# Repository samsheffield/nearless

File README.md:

# Nearless (Nearness 1U Rework)

This is a small Intellijel 1U rework of Nearness designed by [*Jesper Särnesjö*](https://github.com/sarnesjo/nearness).

Minimal panning mixer for the Eurorack modular synthesizer system. Five inputs, two outputs. The closer an input is to either side, the greater its panning in that direction. 10hp.

Nearness is a product of the [*llllllll*](https://llllllll.co/t/prototyping-nearness-a-minimal-panning-mixer-module/8330) community.

## CHANGES

The module has been redesigned to fit an Intellijel 1U in 10hp, so there are two fewer inputs. Why 10hp? That's all I had free! :)

The resistor values have been simplified to accomodate the simple stereo spread. I tried to leave everything else as I found it.

## PCBS AND PANEL

The [kicad](kicad) directory contains the schematic and PCB and panel layouts as KiCad 5 projects.

Gerber files for fabrication are available in the [gerbers](gerbers) directory. 

Here is the [BOM](nearless_BOM.csv).

## IMPORTANT

1. I fabricated a working 0603 vesion of this module but decided to update the footprints to 0805 components before sharing (in kindness to others with bad vision). I have not built the 0805 version personally, but it should be fine. Thanks in advance to anyone willing to look over things/give it a try. Let me know how it goes.
2. On the bottom PCB the jumper pins and power header are on the backside, and the components and pin headers to connect boards are on the top. See [rear pic](doc/rear.jpg) to clarify.

## License

[CC BY-SA 4.0](http://creativecommons.org/licenses/by-sa/4.0/)

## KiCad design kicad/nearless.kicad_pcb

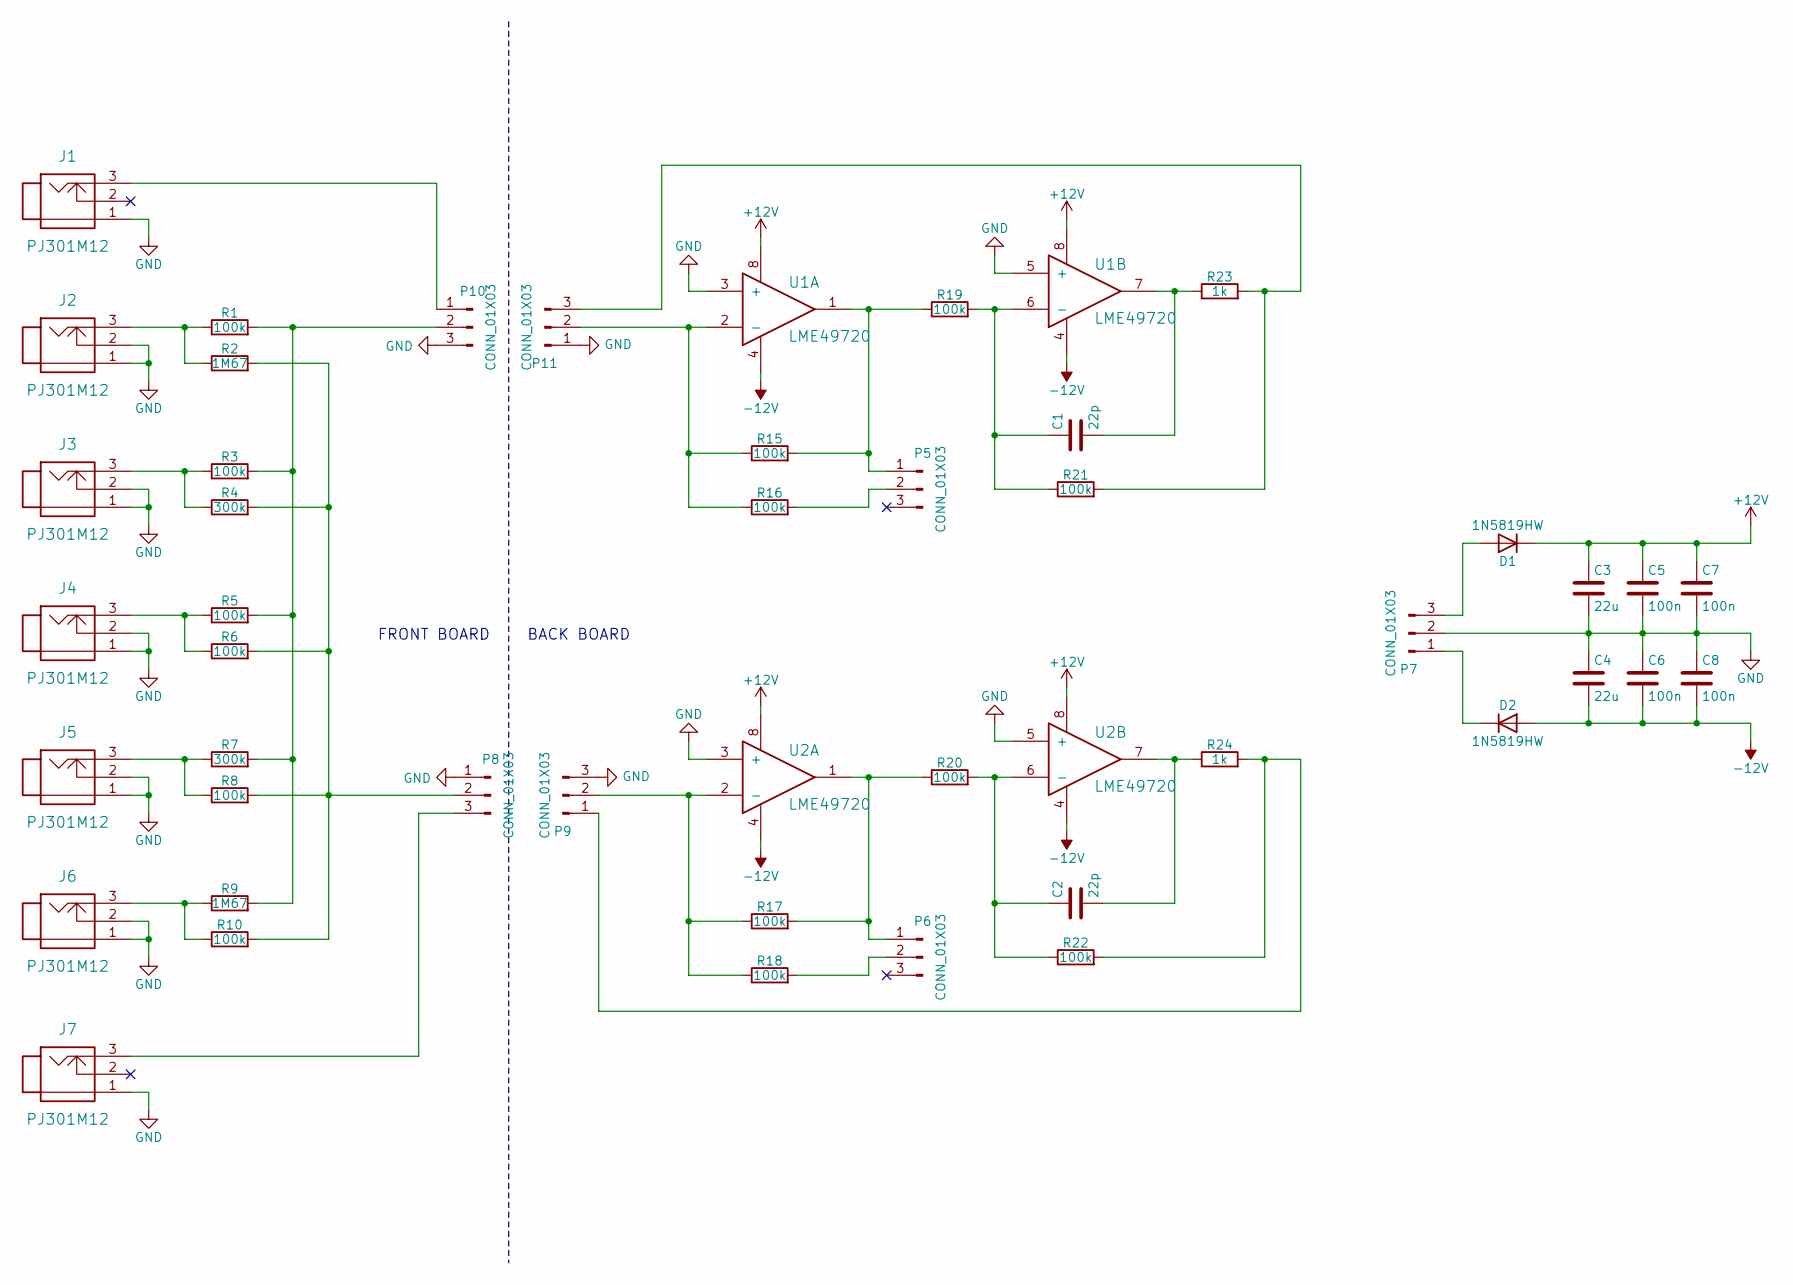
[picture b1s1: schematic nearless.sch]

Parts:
C1, C2: 22p; 0805
C3, C4: 22u; 0805
C5, C6, C7, C8: 100n; 0805
D1, D2: 1N5819HW; SOD-123
J1, J2, J3, J4, J5, J6, J7: PJ301M12
P5, P6, P8, P9, P10, P11: CONN_01X03; Pin_1x3
P7: CONN_01X03; Eurorack_2x5
R1, R3, R5, R6, R8, R10, R15, R16, R17, R18, R19, R20, R21, R22: 100k; 0805
R2, R9: 1M67; 0805
R4, R7: 300k; 0805
R23, R24: 1k; 0805
U1, U2: LME49720; SOIC-8

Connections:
+12V: C3.1, C5.1, C7.1, D1.1 (K), U1.8, U2.8
-12V: C4.2, C6.2, C8.2, D2.2 (A), U1.4, U2.4
GND: C3.2, C4.1, C5.2, C6.1, C7.2, C8.1, J1.1, J2.1, J2.2, J3.1, J3.2, J4.1, J4.2, J5.1, J5.2, J6.1, J6.2, J7.1, P7.2, P8.1, P9.3, P10.3, P11.1, U1.3 (+), U1.5 (+), U2.3 (+), U2.5 (+)
unnamed: C1.1, R19.2, R21.1, U1.6 (-)
unnamed: C1.2, R23.1, U1.7
unnamed: C2.1, R20.2, R22.1, U2.6 (-)
unnamed: C2.2, R24.1, U2.7
unnamed: D1.2 (A), P7.3
unnamed: D2.1 (K), P7.1
unnamed: J1.3, P10.1
unnamed: J2.3, R1.1, R2.1
unnamed: J3.3, R3.1, R4.1
unnamed: J4.3, R5.1, R6.1
unnamed: J5.3, R7.1, R8.1
unnamed: J6.3, R9.1, R10.1
unnamed: J7.3, P8.3
unnamed: P5.1, R15.2, R19.1, U1.1
unnamed: P5.2, R16.2
unnamed: P6.1, R17.2, R20.1, U2.1
unnamed: P6.2, R18.2
unnamed: P8.2, R2.2, R4.2, R6.2, R8.2, R10.2
unnamed: P9.1, R22.2, R24.2
unnamed: P9.2, R17.1, R18.1, U2.2 (-)
unnamed: P10.2, R1.2, R3.2, R5.2, R7.2, R9.2
unnamed: P11.2, R15.1, R16.1, U1.2 (-)
unnamed: P11.3, R21.2, R23.2

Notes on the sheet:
FRONT BOARD
BACK BOARD

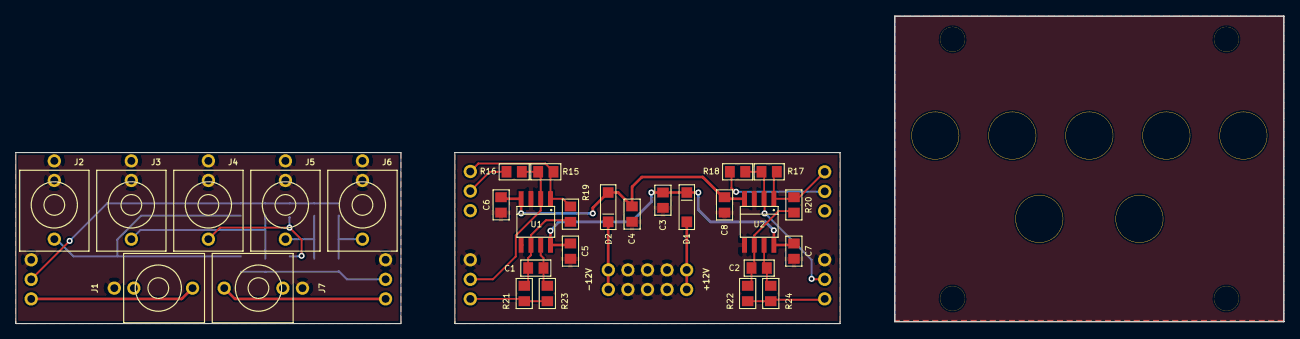
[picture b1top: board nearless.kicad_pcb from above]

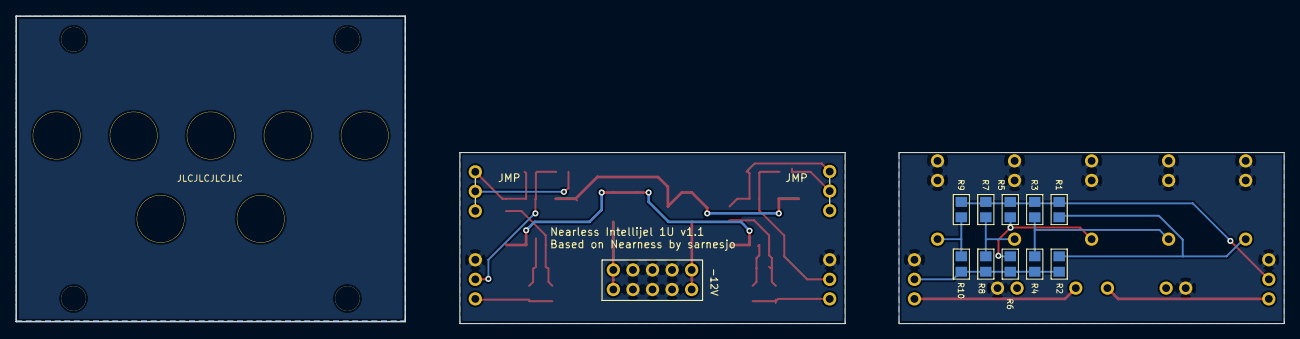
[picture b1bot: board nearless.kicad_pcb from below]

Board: 2 copper layers, 164.6 x 39.9 mm, 57 parts (10 on the bottom side), 26 nets.

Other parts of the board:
JACK: MonoJackHole; MountingHole_6.2mm
JACK#2, JACK#3, JACK#4, JACK#5, JACK#6, JACK#7: MonoJackHole; MountingHole_6.2mm
MNT: PanelMountingHole; MountingHole_3.2mm
MNT#2, MNT#3, MNT#4: PanelMountingHole; MountingHole_3.2mm

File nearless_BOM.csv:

Reference,Quantity,Value,Footprint
C1 C2,2,22p,0805
C3 C4,2,22u,0805
C5 C6 C7 C8,4,100n,0805
D1 D2,2,1N5819HW,SOD-123
J1 J2 J3 J4 J5 J6 J7,7,,Thonkiconn Jack
P5 P6 P8 P10,4,,Header Pin 1x3
P9 P11,2,,Header Socket 1x3
P7,1,,Eurorack Power Header 2x5
R23 R24,2,1k,0805
R1 R3 R5 R6 R8 R10 R15 R16 R17 R18 R19 R20 R21 R22,14,100k,0805
R4 R7,2,300k,0805
R2 R9,2,1M67,0805
U1 U2,2,LME49720,SOIC-8
,2,,Dual Shunt/Jumper

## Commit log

2021-08-08 Added BOM
    Fixed .gitgnore
